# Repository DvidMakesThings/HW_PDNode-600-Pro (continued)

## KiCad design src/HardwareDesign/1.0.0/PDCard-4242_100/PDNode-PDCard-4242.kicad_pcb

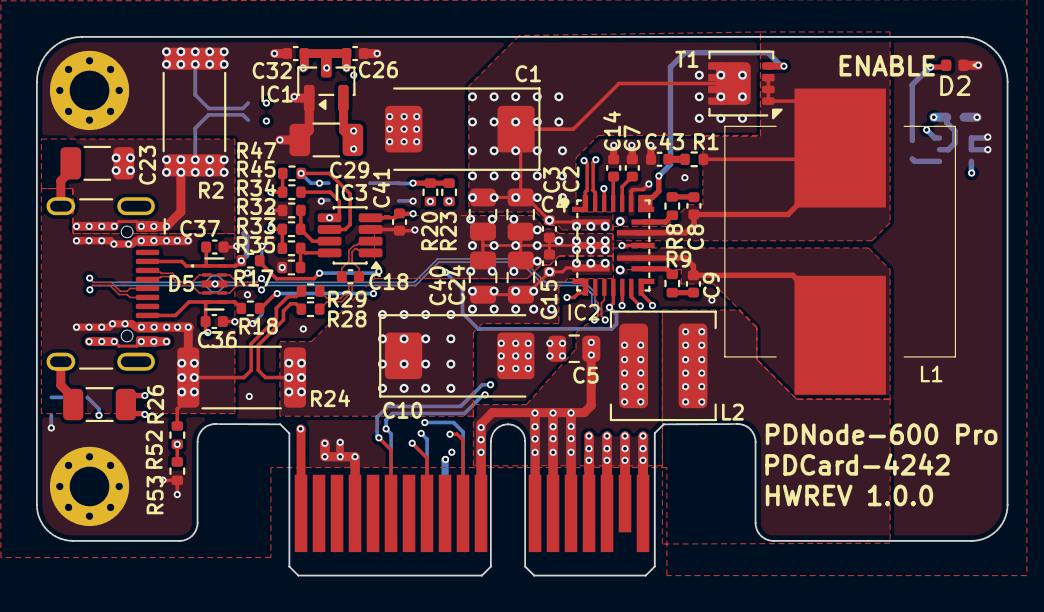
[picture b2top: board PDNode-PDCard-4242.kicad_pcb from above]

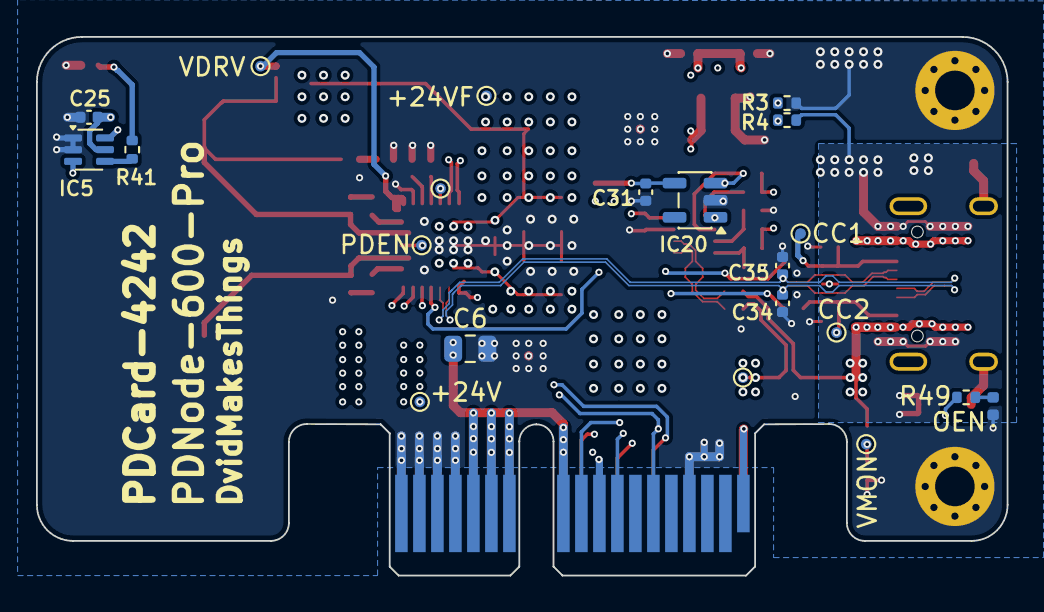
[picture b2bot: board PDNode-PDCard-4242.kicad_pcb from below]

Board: 6 copper layers, 53.9 x 29.9 mm, 75 parts (21 on the bottom side), 40 nets.

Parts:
C1, C10: 100uF 25V; CP_EIA-7343-30_AVX-N
C2, C3, C5, C6: 4.7uF 50V; C_0805_2012Metric
C4, C15, C18, C25, C31, C32, C41: 100nF 50V; C_0402_1005Metric
C7: 2.2uF 25V; C_0402_1005Metric
C8, C9: 220nF 50V; C_0402_1005Metric
C14: 470pF 50V; C_0402_1005Metric
C23: 1nF 2kV; C_1206_3216Metric
C24, C40: 10uF 50V; C_0805_2012Metric
C26: 1uF 50V; C_0402_1005Metric
C29: 10uF 50V; C_1206_3216Metric
C34, C35, C43: 1nF 50V; C_0402_1005Metric
C36, C37: 390pF 50V; C_0402_1005Metric
CC1, CC2: TestPoint_0.6mm
D1: Green; LED_0402_1005Metric
D2: Blue; LED_0402_1005Metric
D5: TPD4EUSB30DQAR; USON10_2.5x1
H1, H2: MountingHole_Pad; MountingHole_2.2mm_M2_Pad_Via
IC1: MCP1702T-3302E/CB; SOT-23
IC2: MPQ4242GVE-0001-AEC1-P; QFN-22_4X5mm
IC3: INA219BIDCNT; SOT-23-8
IC5: SN74LVC1G97QDCKRQ1; SOT-363_SC-70-6
IC20: 24AA02E-OT; SOT-23-5
J1: USB-TYPE-C-018; USB_C_Receptacle_HCTL_HC-TYPE-C-16P-01A
J2: PCIE EDGE CONNECTOR; BUS_PCIexpress_x1
L1: 4.7uH 13A; 7443551470
L2: 2.2uH 9.7A; 5.5x5.3mm_XAL5030-222MEC
PDAT1: TestPoint_0.6mm
PDEN1: TestPoint_0.6mm
PDOUT1: TestPoint_0.6mm
R1, R3, R4, R28, R29: 1R 1%; R_0402_1005Metric
R2: 0.010R 1%; R_2512_6332Metric
R8, R9: 0R 1%; R_0402_1005Metric
R17, R18: 2.2R 1%; R_0402_1005Metric
R20, R23: 100K 1%; R_0402_1005Metric
R24: 0.005R 1% 2W; R_2512_6332Metric
R26: 1M 1%; R_1206_3216Metric
R32, R33, R34, R35, R53: 10K 1%; R_0402_1005Metric
R41, R49: 1K 1%; R_0402_1005Metric
R45, R47: 2.4K 1%; R_0402_1005Metric
R52: 90.9K 1%; R_0402_1005Metric
T1: DMN4008LFG-7; Diodes_PowerDI3333-8
V24, V24F1: TestPoint_0.6mm
VDRV1: TestPoint_0.6mm
VMON1: TestPoint_0.6mm

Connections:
+3.3V: C25.1, C29.1, C31.1, C41.1, IC1.2 (VOUT), IC3.4 (VS), IC5.5 (VCC), IC20.4 (V_{CC}), R20.1, R23.1, R32.1, R33.1, R45.1, R47.1
+5V: C26.1, C32.1, IC1.3 (VIN), IC2.8 (GPIO2), J2.A1, J2.A9, J2.B1
+24V: C5.1, C6.1, J2.A11, J2.A12, J2.A13, J2.A14, J2.B11, J2.B12, J2.B13, J2.B14 (B13), L2.1, V24.1
+24V_FILTERED: C1.1, C2.1, C3.1, C4.1, IC2.1 (VIN), L2.2, T1.5 (D), T1.6 (D), T1.7 (D), T1.8 (D), V24F1.1
/Project Architecture/Board Connector and Supplies/PORT_EN: IC5.6 (IN2), J2.B8, R49.2
/Project Architecture/Board Connector and Supplies/VBUS_VMON_PORT0: J2.B10, R52.2, R53.1, VMON1.1
/Project Architecture/USB-PD Source Controller/CC1: C37.1, CC1.1, D5.1, J1.A5 (CC1), R17.2
/Project Architecture/USB-PD Source Controller/CC2: C36.1, CC2.1, D5.5, J1.B5 (CC2), R18.2
/Project Architecture/USB-PD Source Controller/I2C_SCL: IC2.10 (SCL), IC3.5 (SCL), IC20.1 (SCL), J2.A6, R45.2
/Project Architecture/USB-PD Source Controller/I2C_SDA: IC2.9 (SDA), IC3.6 (SDA), IC20.3 (SDA), J2.B6, R47.2
/Project Architecture/USB-PD Source Controller/ISEN+: IC2.22 (ISENS+), R4.2
/Project Architecture/USB-PD Source Controller/ISEN-: IC2.21 (ISENS-), R3.2
/Project Architecture/USB-PD Source Controller/PD_ATTACH: IC2.20 (GPIO1), J2.A10, PDAT1.1, R23.2
/Project Architecture/USB-PD Source Controller/PD_CC1: IC2.7 (CC1), R17.1
/Project Architecture/USB-PD Source Controller/PD_CC2: IC2.4 (CC2), R18.1
/Project Architecture/USB-PD Source Controller/PD_ENABLE: IC2.13 (EN), IC5.3 (IN0), J2.A8, PDEN1.1, R20.2
/Project Architecture/USB-PD Source Controller/PD_OUT: C10.1, C15.1, C24.1, C40.1, IC2.3 (OUT), PDOUT1.1, R24.1, R28.1
/Project Architecture/USB-PD Source Controller/SW1: C8.1, IC2.14 (SW1), L1.1, R1.1, T1.1 (S), T1.2 (S), T1.3 (S)
/Project Architecture/USB-PD Source Controller/SW2: C9.1, IC2.12 (SW2), L1.2
/Project Architecture/USB-PD Source Controller/USB_D+: C34.1, D5.4, IC2.5 (DP), J1.A6 (D+), J1.B6 (D+)
/Project Architecture/USB-PD Source Controller/USB_D-: C35.1, D5.2, IC2.6 (DM), J1.A7 (D-), J1.B7 (D-)
/Project Architecture/USB-PD Source Controller/VBUS: J1.A4 (VBUS), J1.A9 (VBUS), J1.B4 (VBUS), J1.B9 (VBUS), R24.2, R29.1, R52.1
/Project Architecture/USB-PD Source Controller/VBUS_MEA_N: C18.2, IC3.2 (IN-), R29.2
/Project Architecture/USB-PD Source Controller/VBUS_MEA_P: C18.1, IC3.1 (IN+), R28.2
/Project Architecture/USB-PD Source Controller/VDRV: IC2.16 (HS_G), T1.4 (S), VDRV1.1
GND: C1.2, C2.2, C3.2, C4.2, C5.2, C6.2, C7.2, C10.2, C14.2, C15.2, C24.2, C25.2, C26.2, C29.2, C31.2, C32.2, C34.2, C35.2, C36.2, C37.2, C40.2, C41.2, C43.2, D1.1, D2.1, D5.3, H1.1, H2.1, IC1.1 (GND), IC2.2 (PGND), IC2.17 (AGND), IC3.3 (GND), IC5.1 (IN1), IC5.2 (GND), IC20.2 (V_{SS}), J2.A4, J2.A15, J2.A16, J2.A17, J2.A18, J2.B4, J2.B15, J2.B16, J2.B17, J2.B18, R2.2, R3.1, R34.2, R35.2, R53.2
GND_USB: C23.1, J1.A1 (GND), J1.A12 (GND), J1.B1 (GND), J1.B12 (GND), R2.1, R4.1, R26.1
unnamed: C8.2, R8.2
unnamed: C9.2, R9.2
unnamed: C43.1, R1.2
unnamed: D1.2, R49.1
unnamed: D2.2, R41.2
unnamed: IC2.15 (BST1), R8.1
unnamed: IC2.11 (BST2), R9.1
unnamed: C14.1, IC2.19 (ICOMP)
unnamed: C7.1, IC2.18 (VCC)
unnamed: IC3.7 (A0), R32.2, R34.1
unnamed: IC3.8 (A1), R33.2, R35.1
unnamed: IC5.4 (Y), R41.1
SHIELD: C23.2, J1.S1 (SHIELD), R26.2

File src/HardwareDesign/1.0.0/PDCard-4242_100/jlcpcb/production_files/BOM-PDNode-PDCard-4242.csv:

Comment,Designator,Footprint,LCSC,Quantity
0.005R 1% 2W,R24,R_2512_6332Metric,C108931,1
0.010R 1%,R2,R_2512_6332Metric,C127692,1
0R 1%,"R8,R9",R_0402_1005Metric,C17168,2
100K 1%,"R20,R23",R_0402_1005Metric,C25741,2
100nF 50V,"C15,C18,C25,C32,C4,C41",C_0402_1005Metric,C307331,6
100uF 25V,"C1,C10",CP_EIA-7343-30_AVX-N,C696814,2
10K 1%,"R34,R35,R53",R_0402_1005Metric,C25744,3
10uF 50V,C29,C_1206_3216Metric,C13585,1
10uF 50V,"C24,C40",C_0805_2012Metric,C440198,2
1K 1%,"R41,R49",R_0402_1005Metric,C11702,2
1M 1%,R26,R_1206_3216Metric,C17927,1
1R 1%,"R1,R28,R29,R3,R4",R_0402_1005Metric,C185446,5
1nF 2kV,C23,C_1206_3216Metric,C173242,1
1nF 50V,"C34,C35,C43",C_0402_1005Metric,C14442,3
1uF 50V,C26,C_0402_1005Metric,C1518208,1
2.2R 1%,"R17,R18",R_0402_1005Metric,C25101,2
2.2uF 25V,C7,C_0402_1005Metric,C385032,1
2.2uH 9.7A,L2,5.5x5.3mm_XAL5030-222MEC,C920280,1
220nF 50V,"C8,C9",C_0402_1005Metric,C5159775,2
390pF 50V,"C36,C37",C_0402_1005Metric,C107050,2
4.7uF 50V,"C2,C3,C5,C6",C_0805_2012Metric,C98192,4
4.7uH 13A,L1,7443551470,C1331156,1
470pF 50V,C14,C_0402_1005Metric,C106207,1
90.9K 1%,R52,R_0402_1005Metric,C163452,1
Blue,D2,LED_0402_1005Metric,C22355736,1
DMN4008LFG-7,T1,Diodes_PowerDI3333-8,C6601822,1
Green,D1,LED_0402_1005Metric,C965793,1
INA219BIDCNT,IC3,SOT-23-8,C2653868,1
MCP1702T-3302E/CB,IC1,SOT-23,C33844,1
MPQ4242GVE-0001-AEC1-P,IC2,QFN-22_4X5mm,C37449370,1
SN74LVC1G97QDCKRQ1,IC5,SOT-363_SC-70-6,C179911,1
TPD4EUSB30DQAR,D5,USON10_2.5x1,C5199222,1
USB-TYPE-C-018,J1,USB_C_Receptacle_HCTL_HC-TYPE-C-16P-01A,C2927038,1

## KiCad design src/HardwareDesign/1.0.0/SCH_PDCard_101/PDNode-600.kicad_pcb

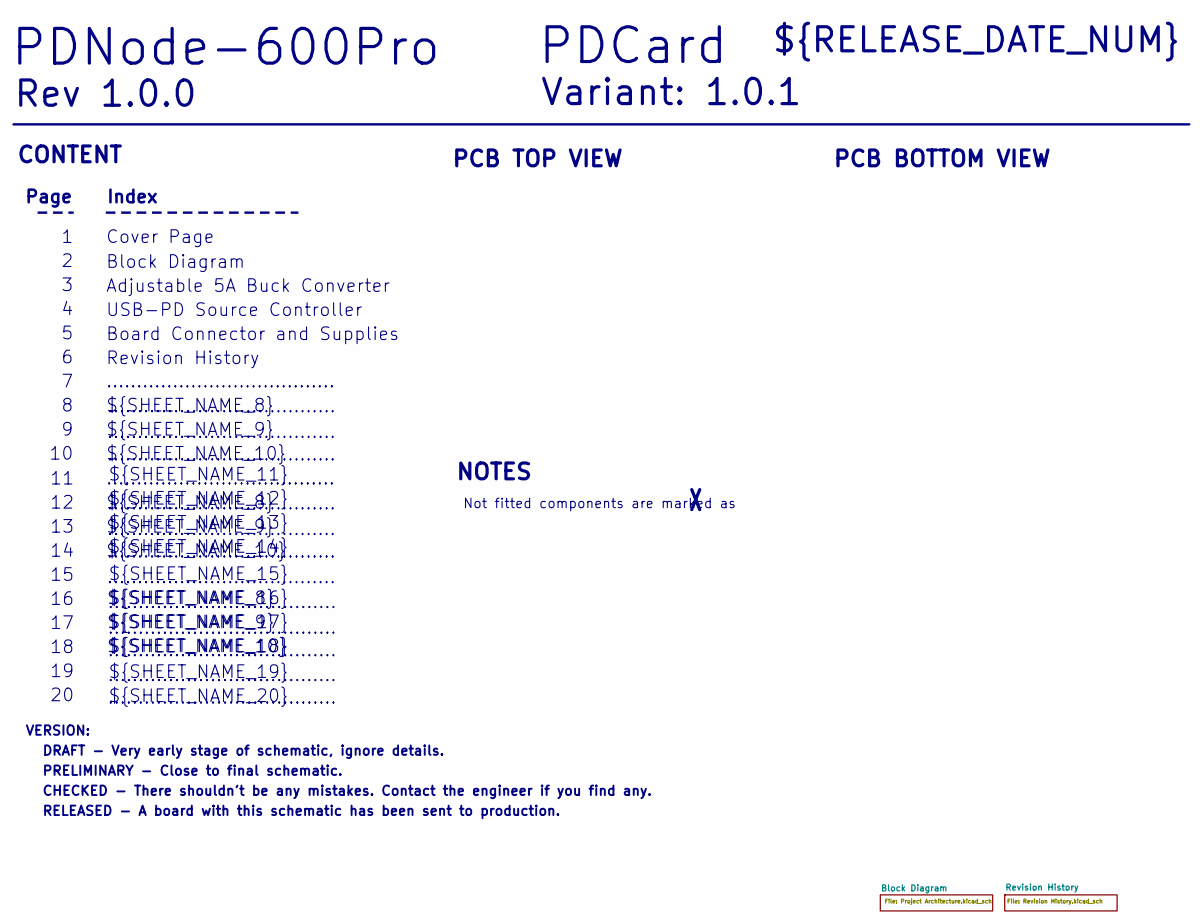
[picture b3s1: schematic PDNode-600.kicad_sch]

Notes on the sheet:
Variant: 1.0.1
RELEASED - A board with this schematic has been sent to production.
${SHEET_NAME_8}
PRELIMINARY - Close to final schematic.
CONTENT
${SHEET_NAME_10}
DRAFT - Very early stage of schematic, ignore details.
${SHEET_NAME_12}
Adjustable 5A Buck Converter
Revision History
${SHEET_NAME_20}
Page
......................................
${RELEASE_DATE_NUM}
Not fitted components are marked as
${SHEET_NAME_11}
Cover Page
${SHEET_NAME_9}
Rev ${REVISION}
${SHEET_NAME_15}
CHECKED - There shouldn't be any mistakes. Contact the engineer if you find any.
PCB BOTTOM VIEW
${SHEET_NAME_14}
${SHEET_NAME_17}
VERSION:
${SHEET_NAME_18}
PDNode-600Pro
NOTES
Block Diagram
${SHEET_NAME_16}
USB-PD Source Controller
${SHEET_NAME_19}
PDCard
PCB TOP VIEW
Index
${SHEET_NAME_13}
Board Connector and Supplies

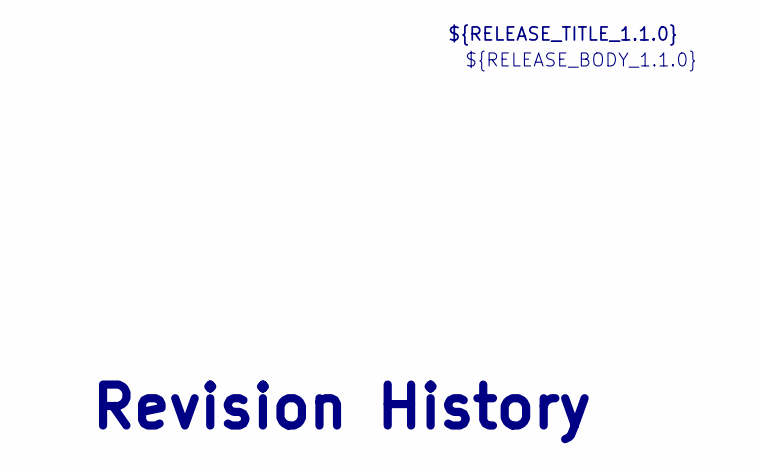
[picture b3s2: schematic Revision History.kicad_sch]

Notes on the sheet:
${RELEASE_BODY_1.1.0}
Revision History
${RELEASE_TITLE_1.1.0}

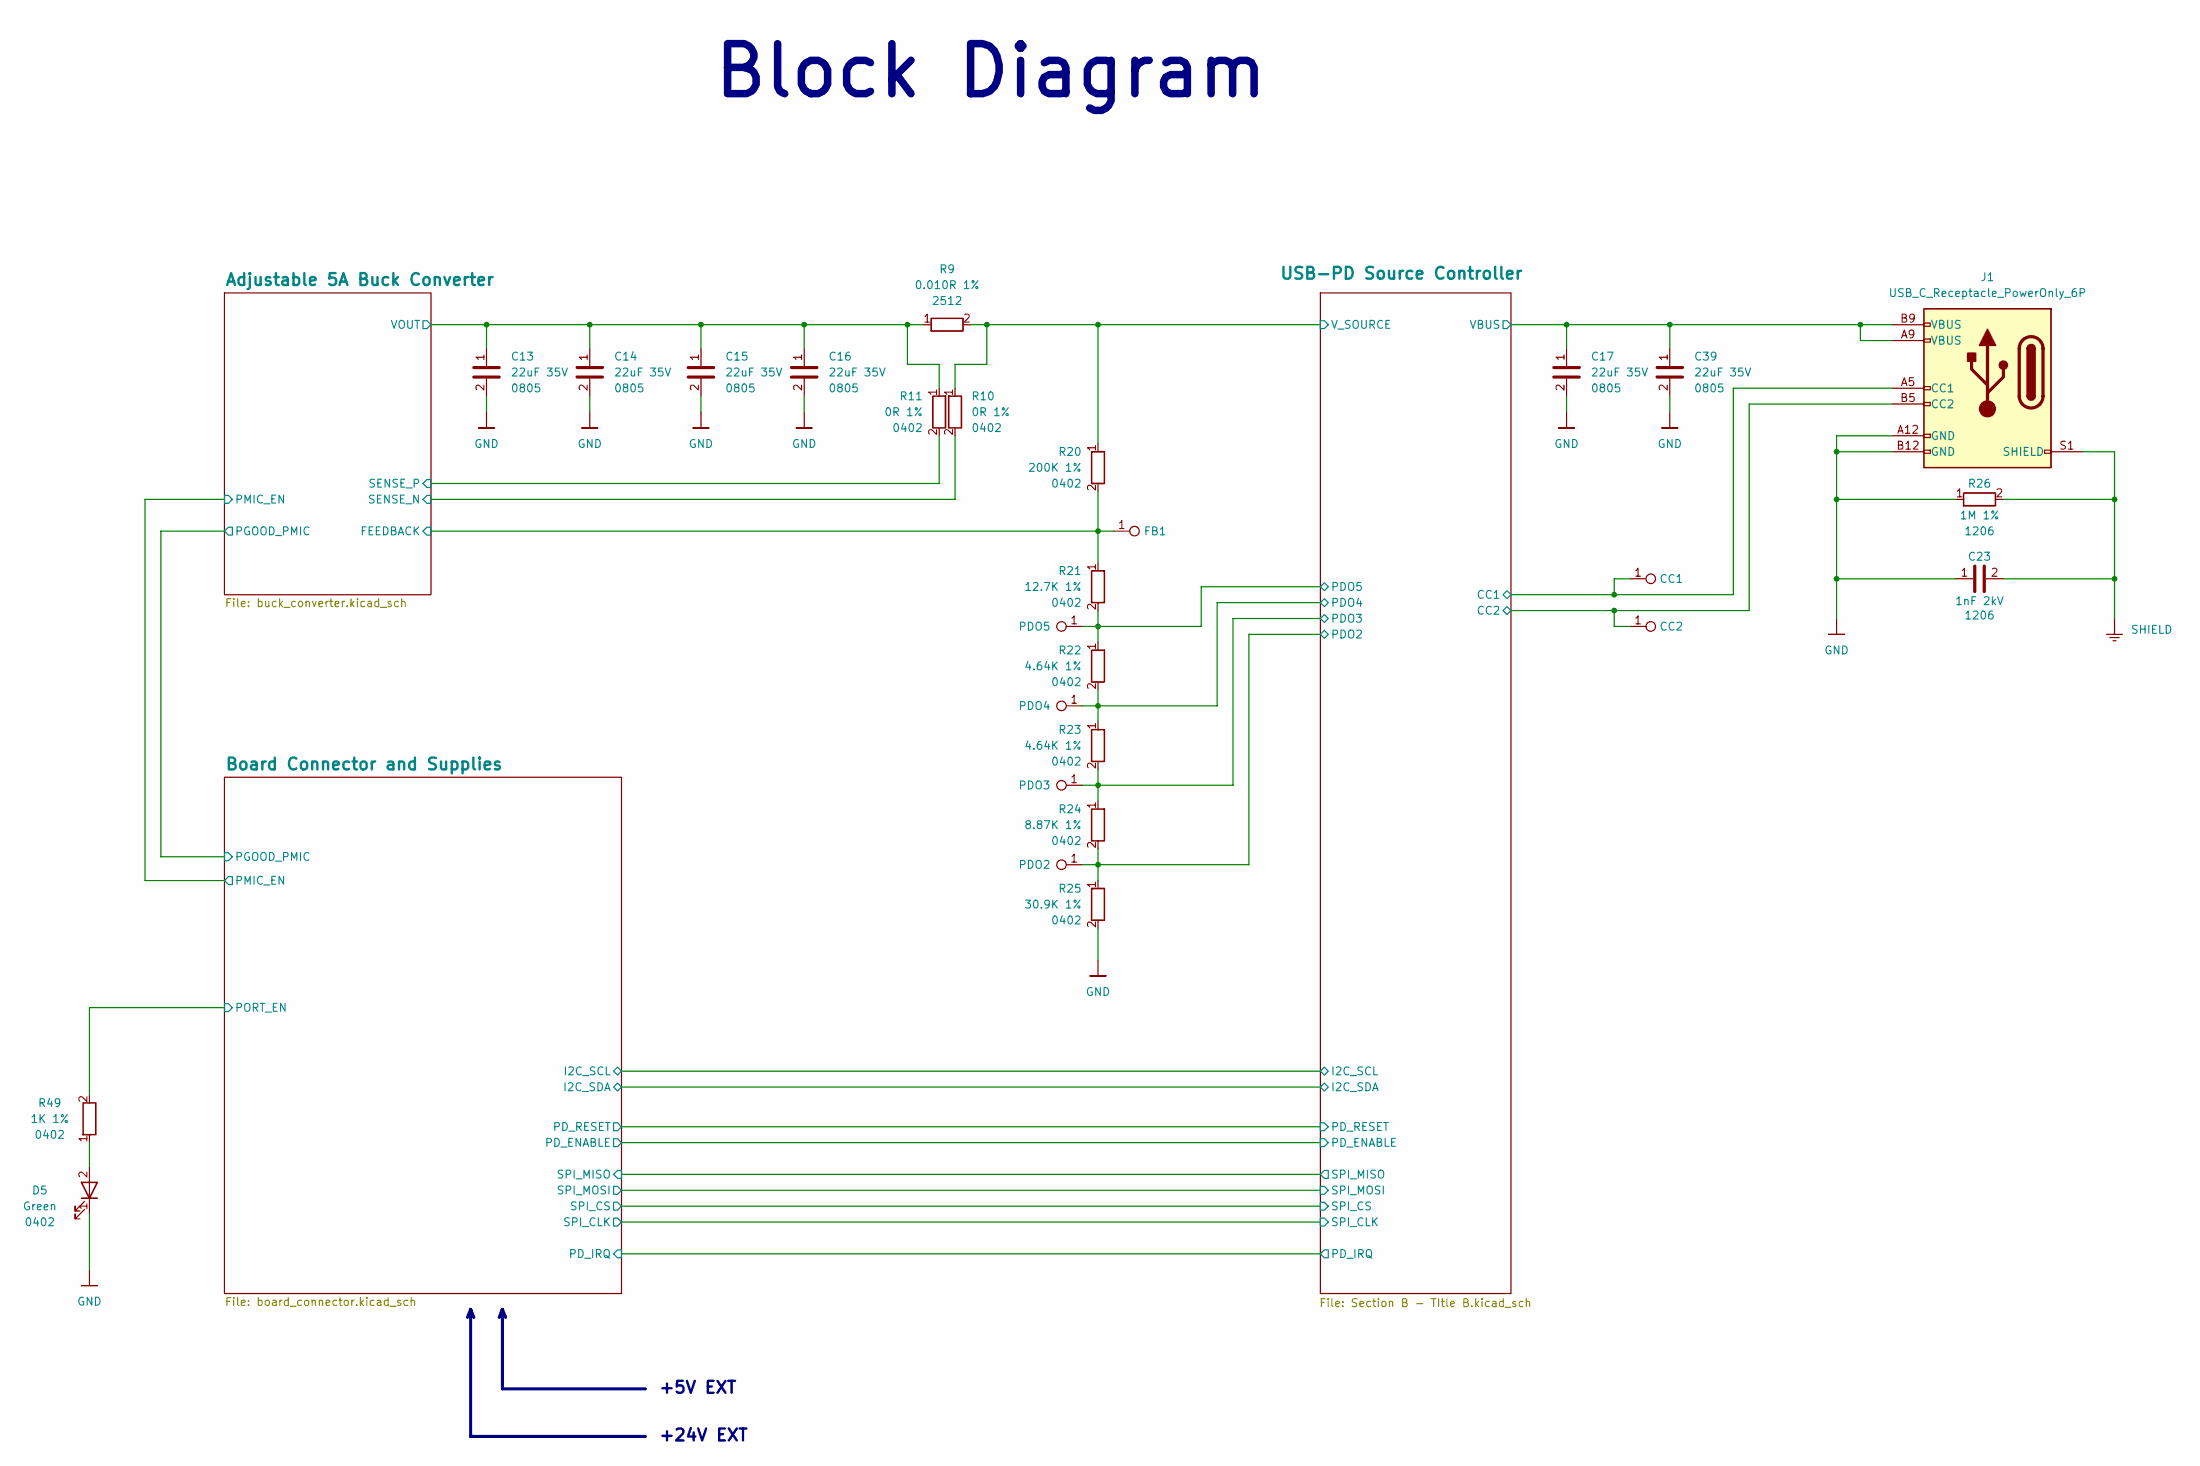
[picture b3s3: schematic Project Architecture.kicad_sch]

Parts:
C13, C14, C15, C16, C17, C39: 22uF 35V; C_0805_2012Metric; MPN CGA0805X5R226M350MT; LCSC_PART C6119901
C23: 1nF 2kV; C_1206_3216Metric; LCSC_PART C173242
CC1, CC2: TestPoint_0.6mm
D5: Green; LED_0402_1005Metric; MPN XL-1005UGC; LCSC_PART C965793
FB1: TestPoint_0.6mm
J1: USB_C_Receptacle_PowerOnly_6P; USB_C_Receptacle_GCT_USB4125-xx-x-0190_6P_TopMnt_Horizontal; MPN USB-TYPE-C-009; LCSC_PART C2927029
PDO2, PDO3, PDO4, PDO5: TestPoint_0.6mm
R9: 0.010R 1%; R_2512_6332Metric; LCSC_PART C127692
R10, R11: 0R 1%; R_0402_1005Metric; LCSC_PART C17168
R20: 200K 1%; R_0402_1005Metric; LCSC_PART C25764
R21: 12.7K 1%; R_0402_1005Metric; LCSC_PART C25853
R22, R23: 4.64K 1%; R_0402_1005Metric; MPN FRC0402F4641TS; LCSC_PART C5153956
R24: 8.87K 1%; R_0402_1005Metric; MPN CL0402FN8K87P; LCSC_PART C48391747
R25: 30.9K 1%; R_0402_1005Metric; LCSC_PART C270615
R26: 1M 1%; R_1206_3216Metric; LCSC_PART C17927
R49: 1K 1%; R_0402_1005Metric; LCSC_PART C11702

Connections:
/Block Diagram/Adjustable 5A Buck Converter/FEEDBACK: FB1.1, R20.2, R21.1; also elsewhere on the board
/Block Diagram/Adjustable 5A Buck Converter/SENSE_N: R10.2; also elsewhere on the board
/Block Diagram/Adjustable 5A Buck Converter/SENSE_P: R11.2; also elsewhere on the board
/Block Diagram/Adjustable 5A Buck Converter/VOUT: C13.1, C14.1, C15.1, C16.1, R9.1, R11.1; also elsewhere on the board
/Block Diagram/Board Connector and Supplies/PORT_EN: R49.2; also elsewhere on the board
/Block Diagram/USB-PD Source Controller/CC1: CC1.1, J1.A5 (CC1); also elsewhere on the board
/Block Diagram/USB-PD Source Controller/CC2: CC2.1, J1.B5 (CC2); also elsewhere on the board
/Block Diagram/USB-PD Source Controller/PDO2: PDO2.1, R24.2, R25.1; also elsewhere on the board
/Block Diagram/USB-PD Source Controller/PDO3: PDO3.1, R23.2, R24.1; also elsewhere on the board
/Block Diagram/USB-PD Source Controller/PDO4: PDO4.1, R22.2, R23.1; also elsewhere on the board
/Block Diagram/USB-PD Source Controller/PDO5: PDO5.1, R21.2, R22.1; also elsewhere on the board
/Block Diagram/USB-PD Source Controller/V_SOURCE: R9.2, R10.1, R20.1; also elsewhere on the board
GND: C13.2, C14.2, C15.2, C16.2, C17.2, C23.1, C39.2, D5.1, J1.A12 (GND), J1.B12 (GND), R25.2, R26.1; also elsewhere on the board
unnamed: D5.2, R49.1
SHIELD: C23.2, J1.S1 (SHIELD), R26.2
VBUS: C17.1, C39.1, J1.A9 (VBUS), J1.B9 (VBUS); also elsewhere on the board

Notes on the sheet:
+5V EXT
+24V EXT
Block Diagram

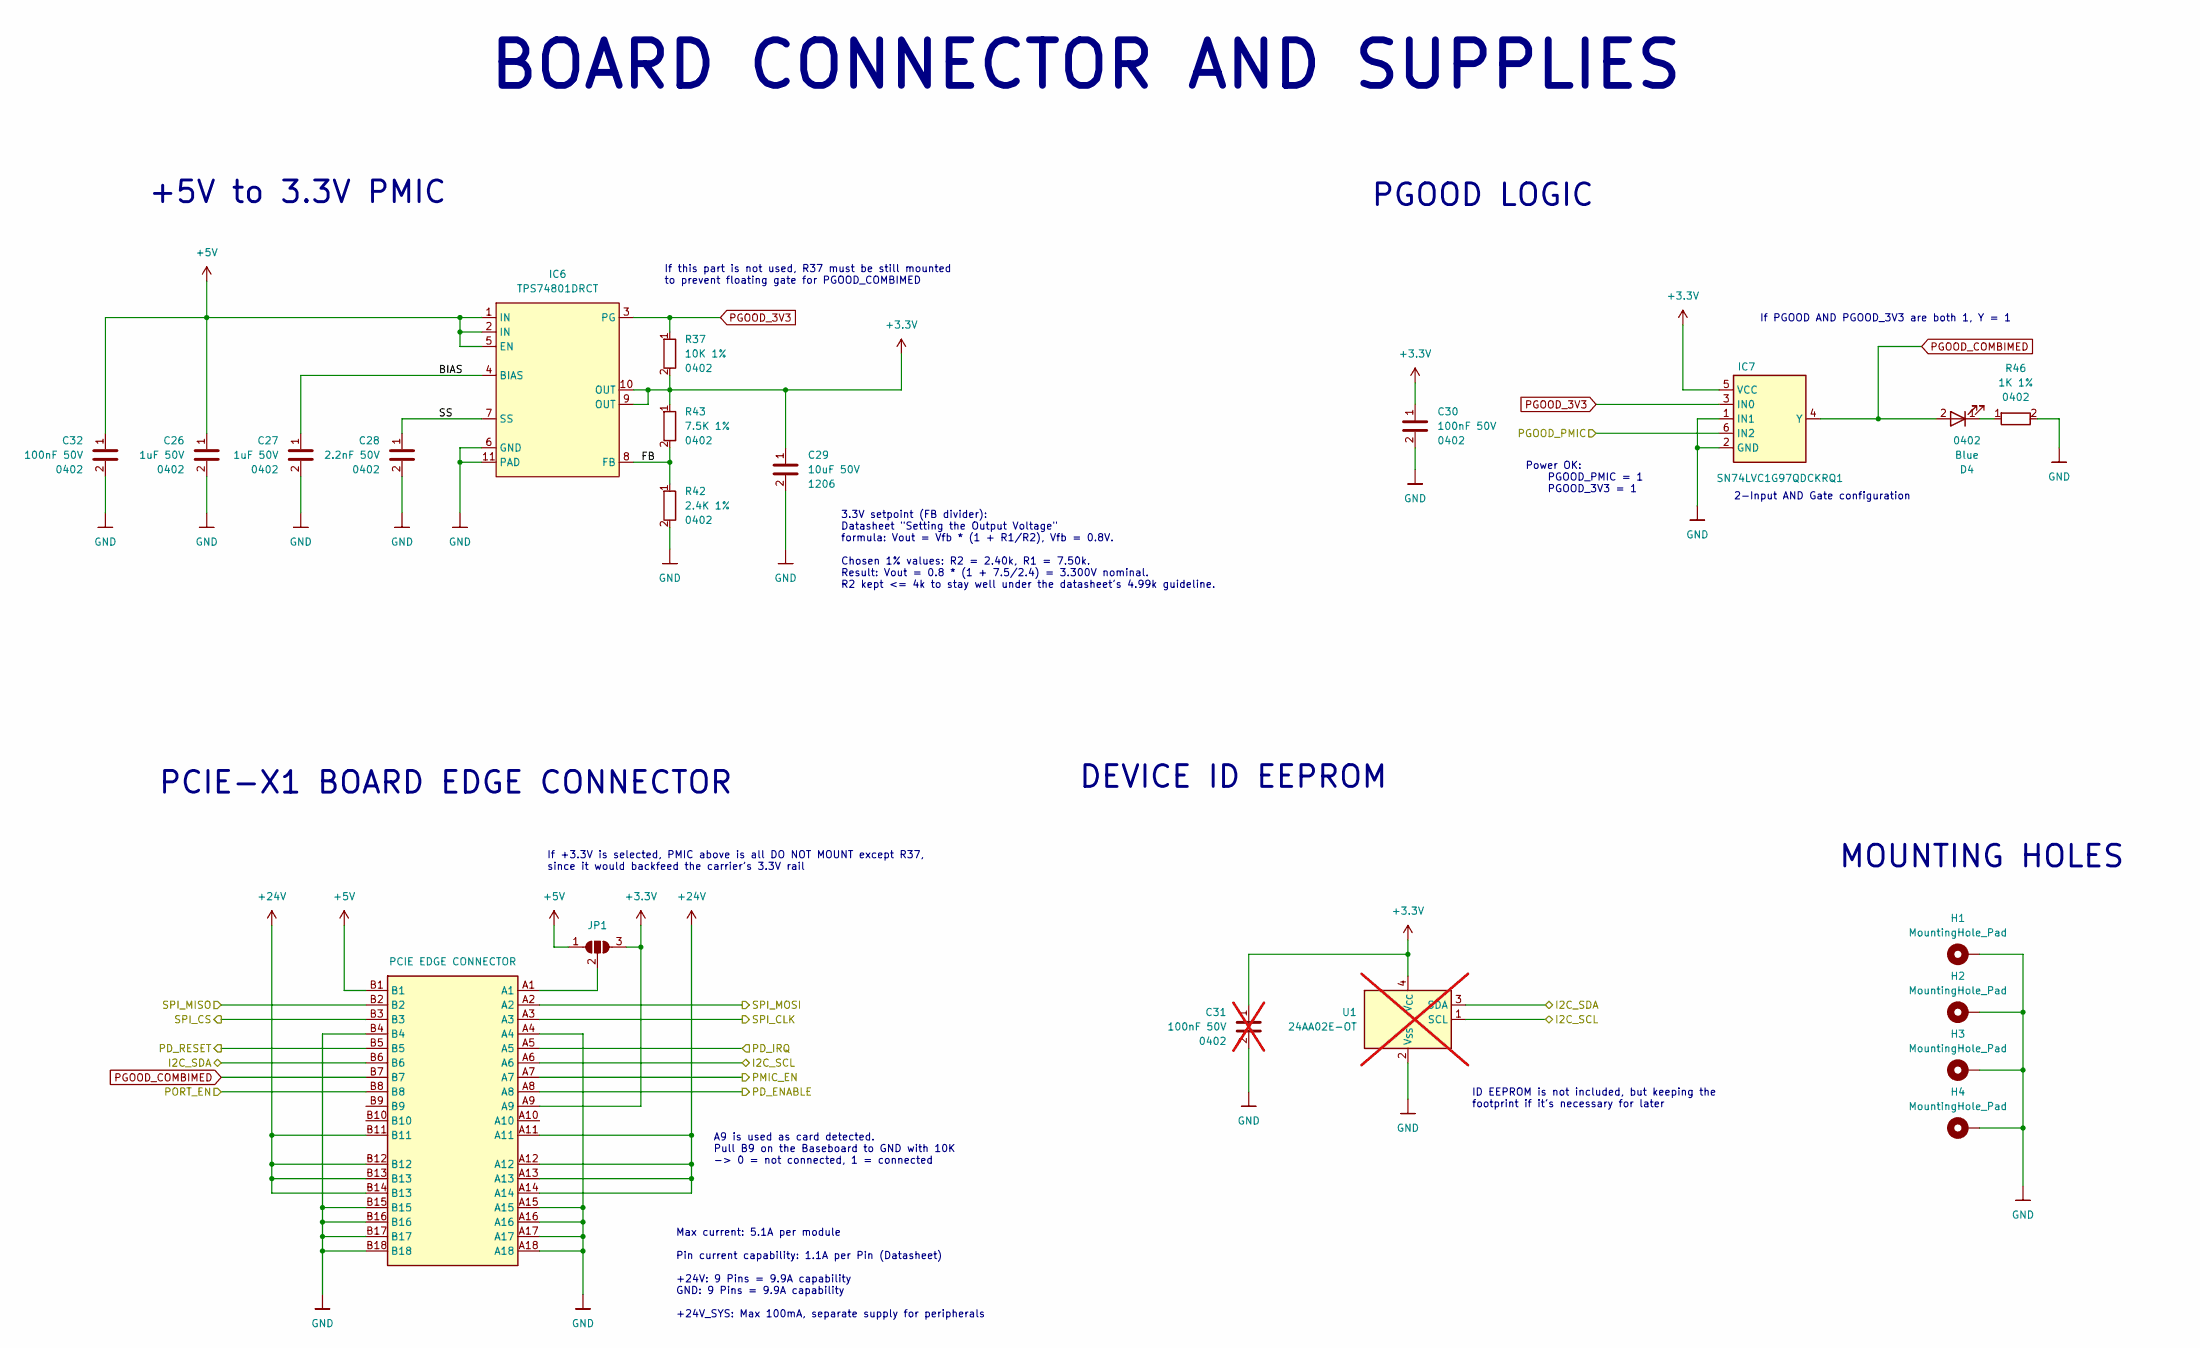
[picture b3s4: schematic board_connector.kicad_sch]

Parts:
C26, C27: 1uF 50V; C_0402_1005Metric; LCSC_PART C1518208
C28: 2.2nF 50V; C_0402_1005Metric; MPN CC0402KRX7R9BB222; LCSC_PART C106861
C29: 10uF 50V; C_1206_3216Metric; MPN CL31A106KBHNNNE; LCSC_PART C13585
C30, C32: 100nF 50V; C_0402_1005Metric; LCSC_PART C307331
C31: 100nF 50V; C_0402_1005Metric; LCSC_PART C307331; not fitted
D4: Blue; LED_0402_1005Metric; MPN XL-1005UBC; LCSC_PART C22355736
H1, H2, H3, H4: MountingHole_Pad; MountingHole_2.2mm_M2_Pad_Via
IC6: TPS74801DRCT; VSON-10-1EP_3x3mm_P0.5mm_EP1.65x2.4mm_ThermalVias; MPN TPS74801DRCT; LCSC_PART C882845
IC7: SN74LVC1G97QDCKRQ1; SOT-363_SC-70-6; MPN SN74LVC1G97QDCKRQ1; LCSC_PART C179911
J2: PCIE EDGE CONNECTOR; BUS_PCIexpress_x1
JP1: SolderJumper_3_Open; SolderJumper-3_P1.3mm_Open_Pad1.0x1.5mm
R37: 10K 1%; R_0402_1005Metric; LCSC_PART C25744
R42: 2.4K 1%; R_0402_1005Metric; LCSC_PART C25882
R43: 7.5K 1%; R_0402_1005Metric; LCSC_PART C25918
R46: 1K 1%; R_0402_1005Metric; LCSC_PART C11702
U1: 24AA02E-OT; SOT-23-5; not fitted

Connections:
+3.3V: C29.1, C30.1, C31.1, IC6.9 (OUT), IC6.10 (OUT), IC7.5 (VCC), J2.A9, JP1.3 (B), R37.2, R43.1, U1.4 (V_{CC}); also elsewhere on the board
+5V: C26.1, C32.1, IC6.1 (IN), IC6.2 (IN), IC6.5 (EN), J2.B1, JP1.1 (A); also elsewhere on the board
+24V: J2.A11, J2.A12, J2.A13, J2.A14, J2.B11, J2.B12, J2.B13, J2.B14 (B13); also elsewhere on the board
/Block Diagram/Board Connector and Supplies/BIAS: C27.1, IC6.4 (BIAS)
/Block Diagram/Board Connector and Supplies/FB: IC6.8 (FB), R42.1, R43.2
/Block Diagram/Board Connector and Supplies/I2C_SCL: J2.A6, U1.1 (SCL); also elsewhere on the board
/Block Diagram/Board Connector and Supplies/I2C_SDA: J2.B6, U1.3 (SDA); also elsewhere on the board
/Block Diagram/Board Connector and Supplies/PORT_EN: J2.B8; also elsewhere on the board
/Block Diagram/Board Connector and Supplies/SS: C28.1, IC6.7 (SS)
/Block Diagram/USB-PD Source Controller/PD_ENABLE: J2.A8; also elsewhere on the board
/Block Diagram/USB-PD Source Controller/PD_IRQ: J2.A5; also elsewhere on the board
/Block Diagram/USB-PD Source Controller/PD_RESET: J2.B5; also elsewhere on the board
/Block Diagram/USB-PD Source Controller/SPI_CLK: J2.A3; also elsewhere on the board
/Block Diagram/USB-PD Source Controller/SPI_CS: J2.B3; also elsewhere on the board
/Block Diagram/USB-PD Source Controller/SPI_MISO: J2.B2; also elsewhere on the board
/Block Diagram/USB-PD Source Controller/SPI_MOSI: J2.A2; also elsewhere on the board
GND: C26.2, C27.2, C28.2, C29.2, C30.2, C31.2, C32.2, H1.1, H2.1, H3.1, H4.1, IC6.6 (GND), IC6.11 (PAD), IC7.1 (IN1), IC7.2 (GND), J2.A4, J2.A15, J2.A16, J2.A17, J2.A18, J2.B4, J2.B15, J2.B16, J2.B17, J2.B18, R42.2, R46.2, U1.2 (V_{SS}); also elsewhere on the board
unnamed: D4.1, R46.1
unnamed: J2.A1, JP1.2 (C)
PGOOD_3V3: IC6.3 (PG), IC7.3 (IN0), R37.1
PGOOD_COMBIMED: D4.2, IC7.4 (Y), J2.B7
PGOOD_PMIC: IC7.6 (IN2); also elsewhere on the board
PMIC_EN: J2.A7; also elsewhere on the board

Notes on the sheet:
ID EEPROM is not included, but keeping the footprint if it's necessary for later
DEVICE ID EEPROM
If this part is not used, R37 must be still mounted to prevent floating gate for PGOOD_COMBIMED
MOUNTING HOLES
If +3.3V is selected, PMIC above is all DO NOT MOUNT except R37, since it would backfeed the carrier's 3.3V rail
Max current: 5.1A per module Pin current capability: 1.1A per Pin (Datasheet) +24V: 9 Pins = 9.9A capability GND: 9 Pins = 9.9A capability +24V_SYS: Max 100mA, separate supply for peripherals
Power OK: PGOOD_PMIC = 1 PGOOD_3V3 = 1
A9 is used as card detected. Pull B9 on the Baseboard to GND with 10K -> 0 = not connected, 1 = connected
If PGOOD AND PGOOD_3V3 are both 1, Y = 1
+5V to 3.3V PMIC
3.3V setpoint (FB divider): Datasheet "Setting the Output Voltage" formula: Vout = Vfb * (1 + R1/R2), Vfb = 0.8V. Chosen 1% values: R2 = 2.40k, R1 = 7.50k. Result: Vout = 0.8 * (1 + 7.5/2.4) = 3.300V nominal. R2 kept <= 4k to stay well under the datasheet's 4.99k guideline.
PCIE-X1 BOARD EDGE CONNECTOR
PGOOD LOGIC
2-Input AND Gate configuration
BOARD CONNECTOR AND SUPPLIES

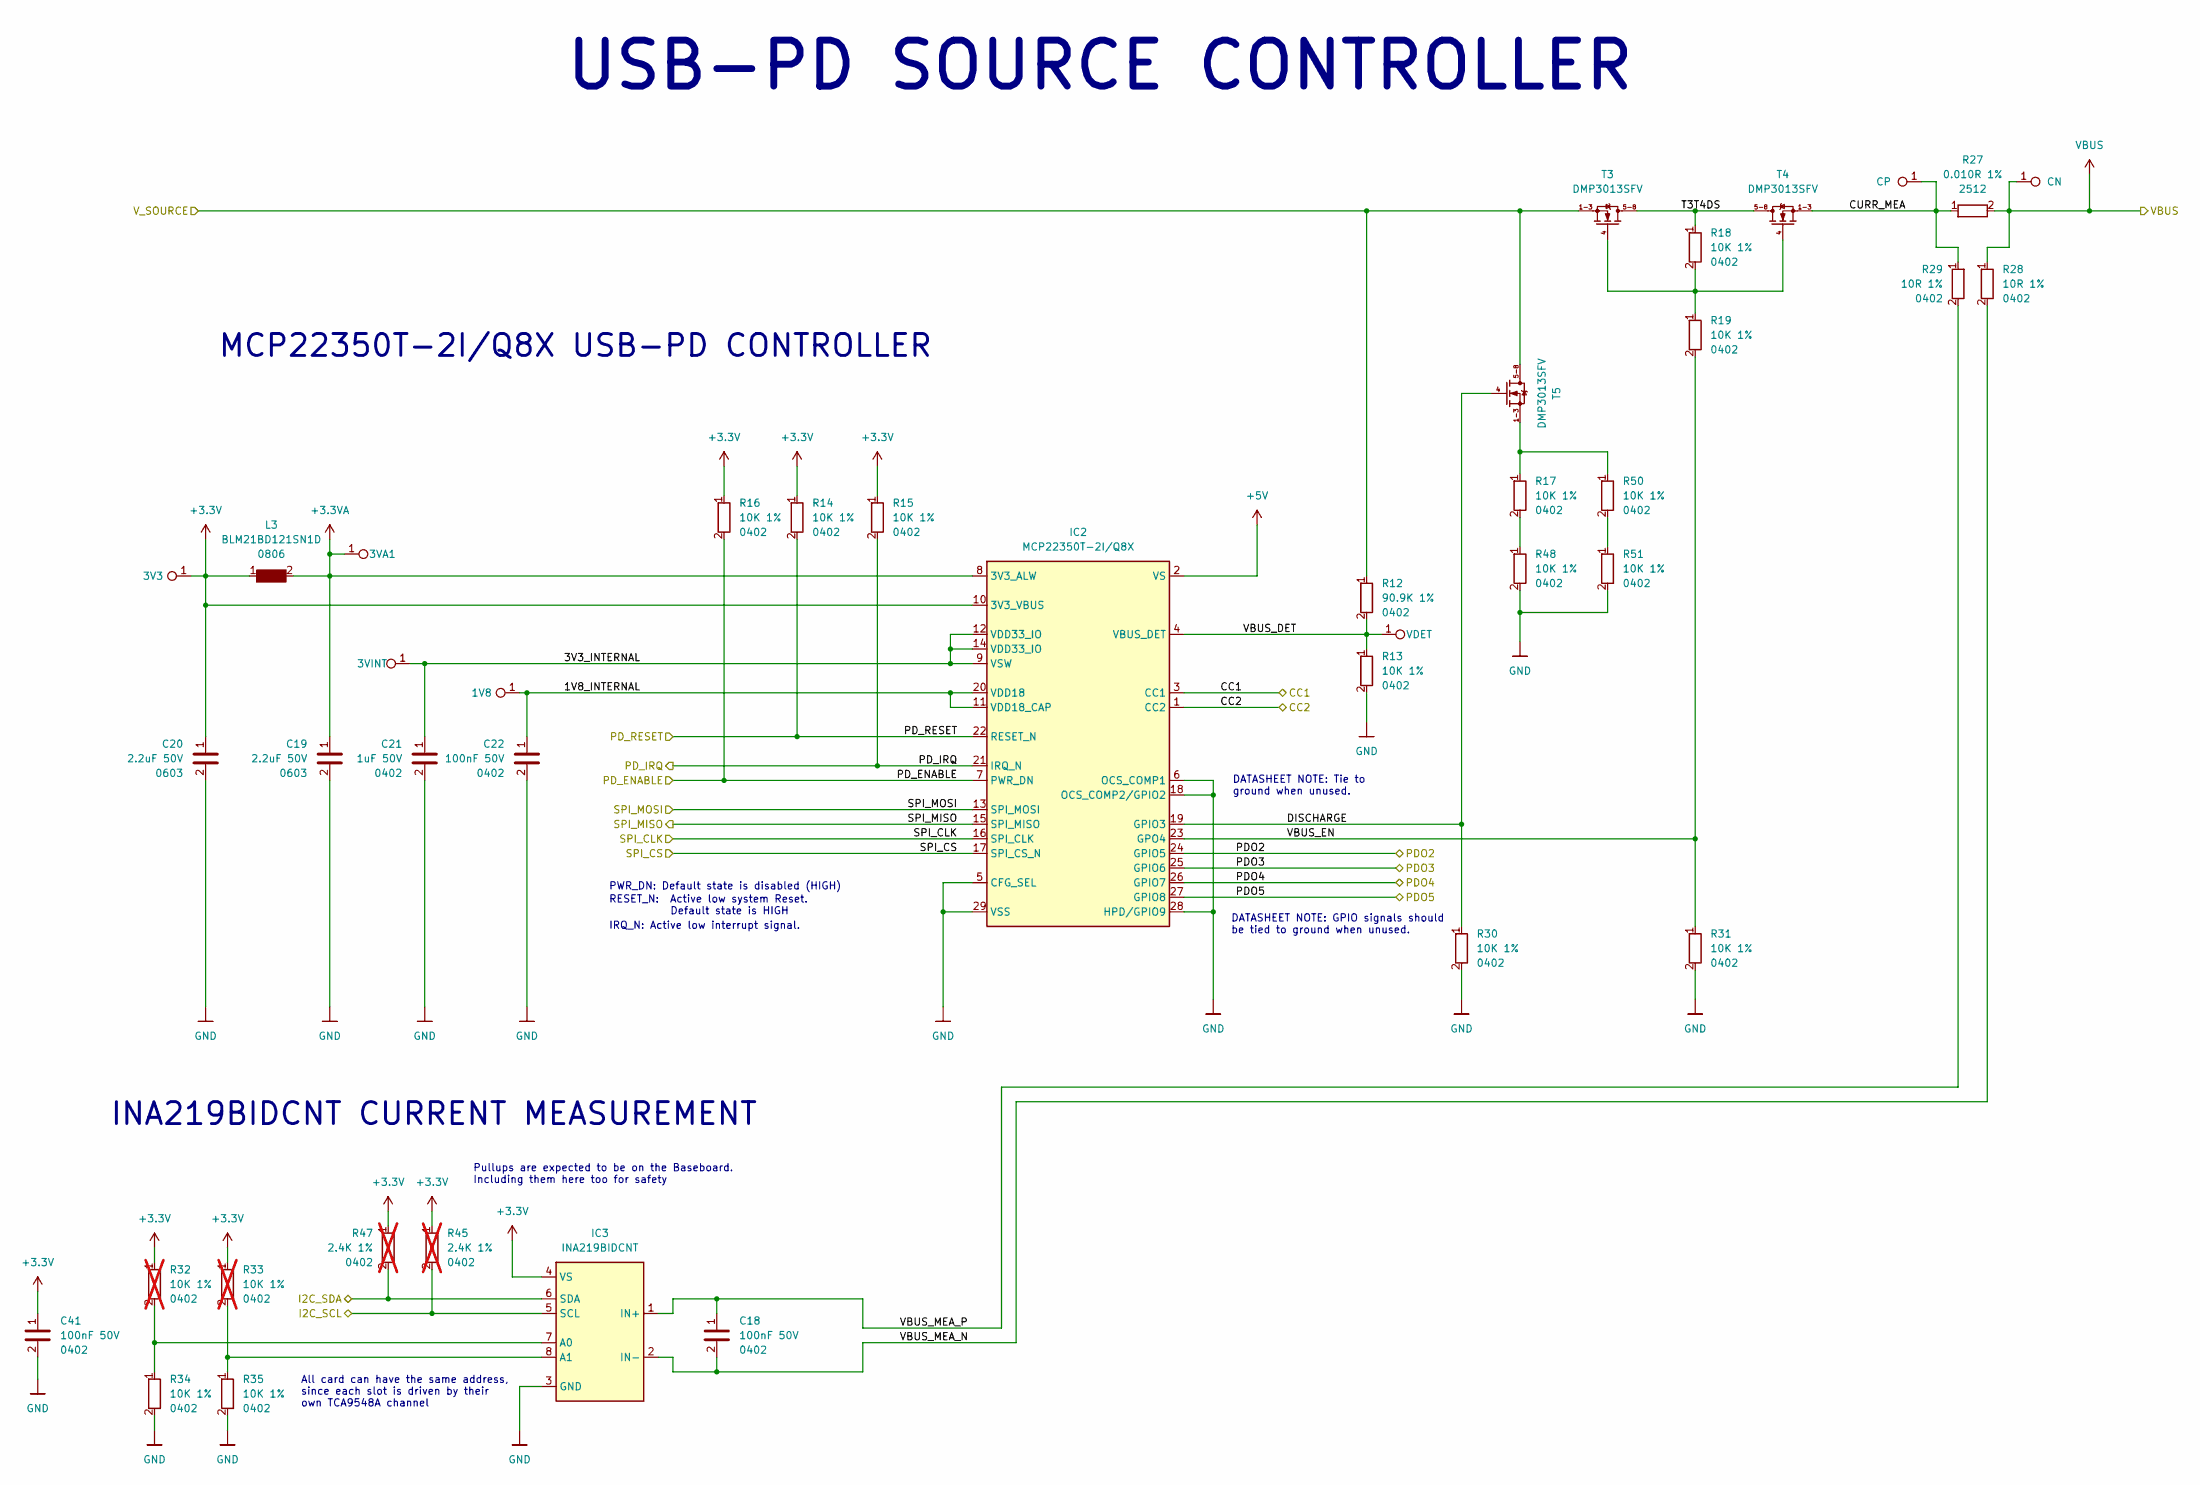
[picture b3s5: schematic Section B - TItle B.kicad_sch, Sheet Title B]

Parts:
1V8, 3V3, 3VA1, 3VINT: TestPoint_0.6mm
C18, C22, C41: 100nF 50V; C_0402_1005Metric; LCSC_PART C307331
C19, C20: 2.2uF 50V; C_0603_1608Metric; LCSC_PART C913904
C21: 1uF 50V; C_0402_1005Metric; LCSC_PART C1518208
CN: TestPoint_0.6mm
CP: TestPoint_0.6mm
IC2: MCP22350T-2I/Q8X; QFN-28-1EP_4x4mm_P0.4mm_EP2.6x2.6mm_ThermalVias; MPN MCP22350T-2I/Q8X; LCSC_PART C38202699
IC3: INA219BIDCNT; SOT-23-8; MPN INA219BIDCNT; LCSC_PART C2653868
L3: BLM21BD121SN1D; R_0805_2012Metric; MPN BLM21BD121SN1D; LCSC_PART C1235333
R12: 90.9K 1%; R_0402_1005Metric; MPN RC0402FR-0790K9L; LCSC_PART C163452
R13, R14, R15, R16, R17, R18, R19, R30, R31, R34, R35, R48, R50, R51: 10K 1%; R_0402_1005Metric; LCSC_PART C25744
R27: 0.010R 1%; R_2512_6332Metric; LCSC_PART C127692
R28, R29: 10R 1%; R_0402_1005Metric; LCSC_PART C25077
R32, R33: 10K 1%; R_0402_1005Metric; LCSC_PART C25744; not fitted
R45, R47: 2.4K 1%; R_0402_1005Metric; LCSC_PART C25882; not fitted
T3, T4, T5: DMP3013SFV; Diodes_PowerDI3333-8; MPN DMP3013SFV; LCSC_PART C264098
VDET: TestPoint_0.6mm

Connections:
+3.3V: 3V3.1, C20.1, C41.1, IC2.10 (3V3_VBUS), IC3.4 (VS), L3.1, R14.1, R15.1, R16.1, R32.1, R33.1, R45.1, R47.1; also elsewhere on the board
+3.3VA: 3VA1.1, C19.1, IC2.8 (3V3_ALW), L3.2
+5V: IC2.2 (VS); also elsewhere on the board
/Block Diagram/Board Connector and Supplies/I2C_SCL: IC3.5 (SCL), R45.2; also elsewhere on the board
/Block Diagram/Board Connector and Supplies/I2C_SDA: IC3.6 (SDA), R47.2; also elsewhere on the board
/Block Diagram/USB-PD Source Controller/1V8_INTERNAL: 1V8.1, C22.1, IC2.11 (VDD18_CAP), IC2.20 (VDD18)
/Block Diagram/USB-PD Source Controller/3V3_INTERNAL: 3VINT.1, C21.1, IC2.9 (VSW), IC2.12 (VDD33_IO), IC2.14 (VDD33_IO); also elsewhere on the board
/Block Diagram/USB-PD Source Controller/CC1: IC2.3 (CC1); also elsewhere on the board
/Block Diagram/USB-PD Source Controller/CC2: IC2.1 (CC2); also elsewhere on the board
/Block Diagram/USB-PD Source Controller/CURR_MEA: CP.1, R27.1, R29.1, T4.1-3; also elsewhere on the board
/Block Diagram/USB-PD Source Controller/DISCHARGE: IC2.19 (GPIO3), R30.1, T5.4
/Block Diagram/USB-PD Source Controller/PDO2: IC2.24 (GPIO5); also elsewhere on the board
/Block Diagram/USB-PD Source Controller/PDO3: IC2.25 (GPIO6); also elsewhere on the board
/Block Diagram/USB-PD Source Controller/PDO4: IC2.26 (GPIO7); also elsewhere on the board
/Block Diagram/USB-PD Source Controller/PDO5: IC2.27 (GPIO8); also elsewhere on the board
/Block Diagram/USB-PD Source Controller/PD_ENABLE: IC2.7 (PWR_DN), R16.2; also elsewhere on the board
/Block Diagram/USB-PD Source Controller/PD_IRQ: IC2.21 (IRQ_N), R15.2; also elsewhere on the board
/Block Diagram/USB-PD Source Controller/PD_RESET: IC2.22 (RESET_N), R14.2; also elsewhere on the board
/Block Diagram/USB-PD Source Controller/SPI_CLK: IC2.16 (SPI_CLK); also elsewhere on the board
/Block Diagram/USB-PD Source Controller/SPI_CS: IC2.17 (SPI_CS_N); also elsewhere on the board
/Block Diagram/USB-PD Source Controller/SPI_MISO: IC2.15 (SPI_MISO); also elsewhere on the board
/Block Diagram/USB-PD Source Controller/SPI_MOSI: IC2.13 (SPI_MOSI); also elsewhere on the board
/Block Diagram/USB-PD Source Controller/T3T4DS: R18.1, T3.5-8, T4.5-8
/Block Diagram/USB-PD Source Controller/VBUS_DET: IC2.4 (VBUS_DET), R12.2, R13.1, VDET.1; also elsewhere on the board
/Block Diagram/USB-PD Source Controller/VBUS_EN: IC2.23 (GPO4), R19.2, R31.1
/Block Diagram/USB-PD Source Controller/VBUS_MEA_N: C18.2, IC3.2 (IN-), R28.2
/Block Diagram/USB-PD Source Controller/VBUS_MEA_P: C18.1, IC3.1 (IN+), R29.2
/Block Diagram/USB-PD Source Controller/V_SOURCE: R12.1, T3.1-3, T5.5-8; also elsewhere on the board
GND: C19.2, C20.2, C21.2, C22.2, C41.2, IC2.5 (CFG_SEL), IC2.6 (OCS_COMP1), IC2.18 (OCS_COMP2/GPIO2), IC2.28 (HPD/GPIO9), IC2.29 (VSS), IC3.3 (GND), R13.2, R30.2, R31.2, R34.2, R35.2, R48.2, R51.2; also elsewhere on the board
unnamed: IC3.7 (A0), R32.2, R34.1
unnamed: IC3.8 (A1), R33.2, R35.1
unnamed: R17.1, R50.1, T5.1-3
unnamed: R17.2, R48.1
unnamed: R18.2, R19.1, T3.4, T4.4
unnamed: R50.2, R51.1
VBUS: CN.1, R27.2, R28.1; also elsewhere on the board

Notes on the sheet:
DATASHEET NOTE: Tie to ground when unused.
MCP22350T-2I/Q8X USB-PD CONTROLLER
PWR_DN: Default state is disabled (HIGH)
Pullups are expected to be on the Baseboard. Including them here too for safety
RESET_N: Active low system Reset. Default state is HIGH
DATASHEET NOTE: GPIO signals should be tied to ground when unused.
All card can have the same address, since each slot is driven by their own TCA9548A channel
IRQ_N: Active low interrupt signal.
INA219BIDCNT CURRENT MEASUREMENT
USB-PD SOURCE CONTROLLER
